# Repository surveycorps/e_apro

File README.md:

e_apro
======

The electrical subsytems schematics, BOM, board files
- usb_hub is a 7 port usb hub based off of TI's TUSB2077A
- audio is a usb audio codec based off the PCM2912A
- gps is a usb powered gps module based off the Jupiter SE880
- screen is a hdmi to tft screen converter using TFP401A
- motor is a motor driver with F2V converters
- powers provides power regulator based off LM3478
- apro_lib contains all the custom symbols and footprints used
- eagle contains the files for connecting the various breakoutboards

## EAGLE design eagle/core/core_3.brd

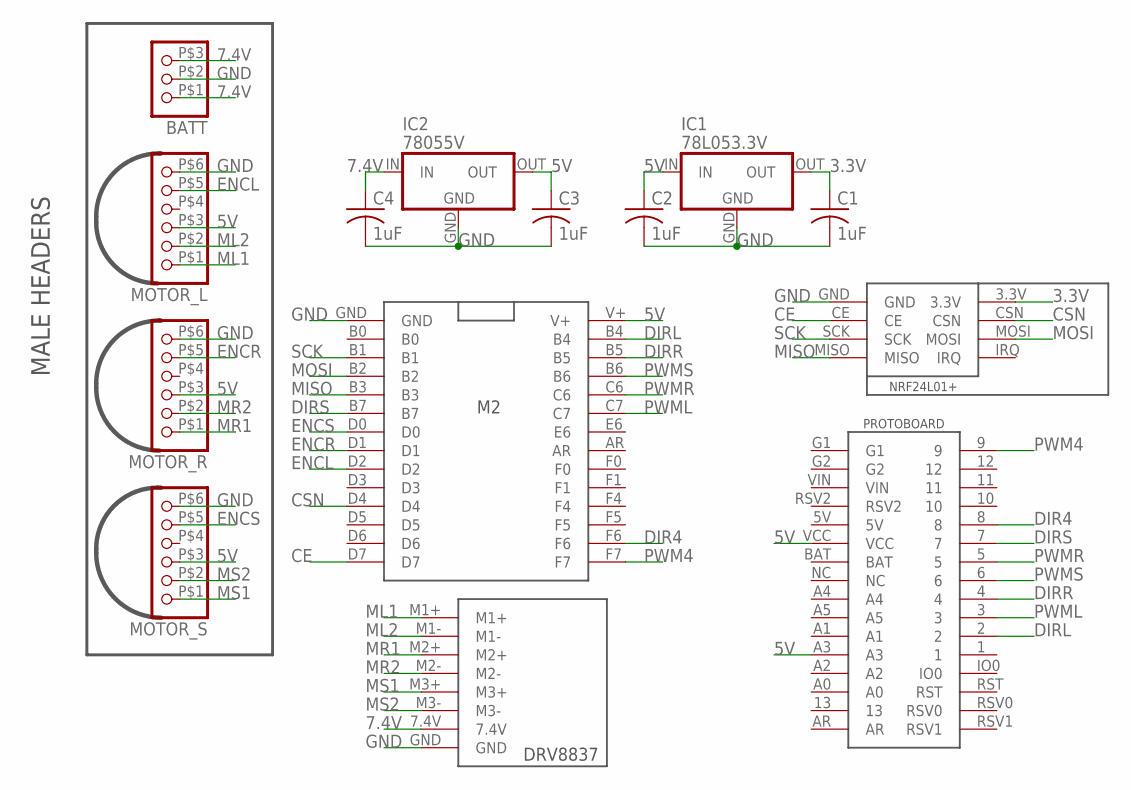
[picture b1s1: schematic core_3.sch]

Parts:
BATT: PINHD-1X3SMD; 1X3/90SMD
C1, C2, C3, C4: 1uF; C025-030X050
IC1: 78L053.3V; TO92
IC2: 78055V; TO220H
MOTOR_L: PINHD-1X6SMD; 1X6/90SMD
MOTOR_R: PINHD-1X6SMD; 1X6/90SMD
MOTOR_S: PINHD-1X6SMD; 1X6/90SMD
U$1: NRF24L01
U$2: M2
U$3: PROTOBOARDSMD; PROTOSMD
U$4: DRV8837

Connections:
3.3V: C1.1, IC1.OUT, U$1.3.3V
5V: C2.1, C3.1, IC1.IN, IC2.OUT, MOTOR_L.P$3 (3), MOTOR_R.P$3 (3), MOTOR_S.P$3 (3), U$2.V+, U$3.A3, U$3.VCC
7.4V: BATT.P$1 (1), BATT.P$3 (3), C4.1, IC2.IN, U$4.7.4V
CE: U$1.CE, U$2.D7
CSN: U$1.CSN, U$2.D4
DIR4: U$2.F6, U$3.8
DIRL: U$2.B4, U$3.2
DIRR: U$2.B5, U$3.4
DIRS: U$2.B7, U$3.7
ENCL: MOTOR_L.P$5 (5), U$2.D2
ENCR: MOTOR_R.P$5 (5), U$2.D1
ENCS: MOTOR_S.P$5 (5), U$2.D0
GND: BATT.P$2 (2), C1.2, C2.2, C3.2, C4.2, IC1.GND, IC2.GND, MOTOR_L.P$6 (6), MOTOR_R.P$6 (6), MOTOR_S.P$6 (6), U$1.GND, U$2.GND, U$4.GND
MISO: U$1.MISO, U$2.B3
ML1: MOTOR_L.P$1 (1), U$4.M1+
ML2: MOTOR_L.P$2 (2), U$4.M1-
MOSI: U$1.MOSI, U$2.B2
MR1: MOTOR_R.P$1 (1), U$4.M2+
MR2: MOTOR_R.P$2 (2), U$4.M2-
MS1: MOTOR_S.P$1 (1), U$4.M3+
MS2: MOTOR_S.P$2 (2), U$4.M3-
PWM4: U$2.F7, U$3.9
PWML: U$2.C7, U$3.3
PWMR: U$2.C6, U$3.5
PWMS: U$2.B6, U$3.6
SCK: U$1.SCK, U$2.B1

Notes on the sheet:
MALE HEADERS

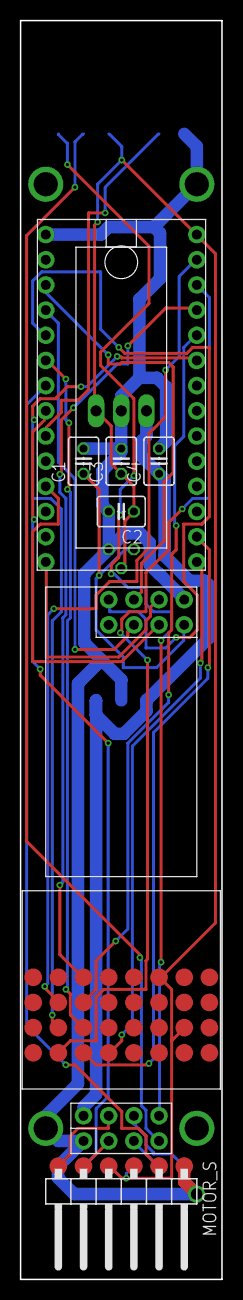
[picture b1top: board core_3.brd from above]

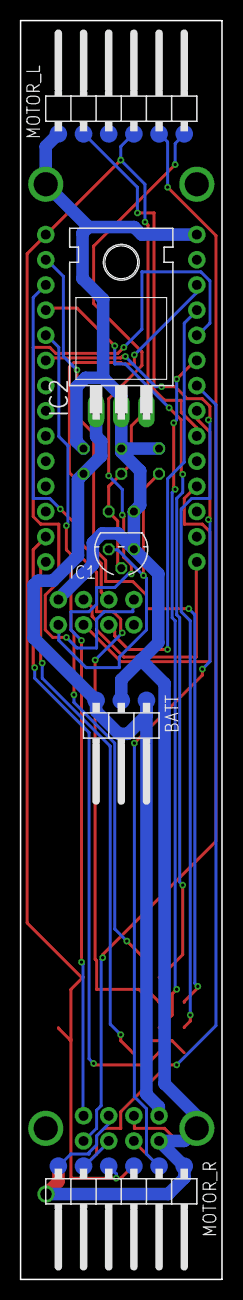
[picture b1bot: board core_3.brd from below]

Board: 2 copper layers, 20.3 x 127.0 mm, 14 parts (5 on the bottom side), 26 nets.

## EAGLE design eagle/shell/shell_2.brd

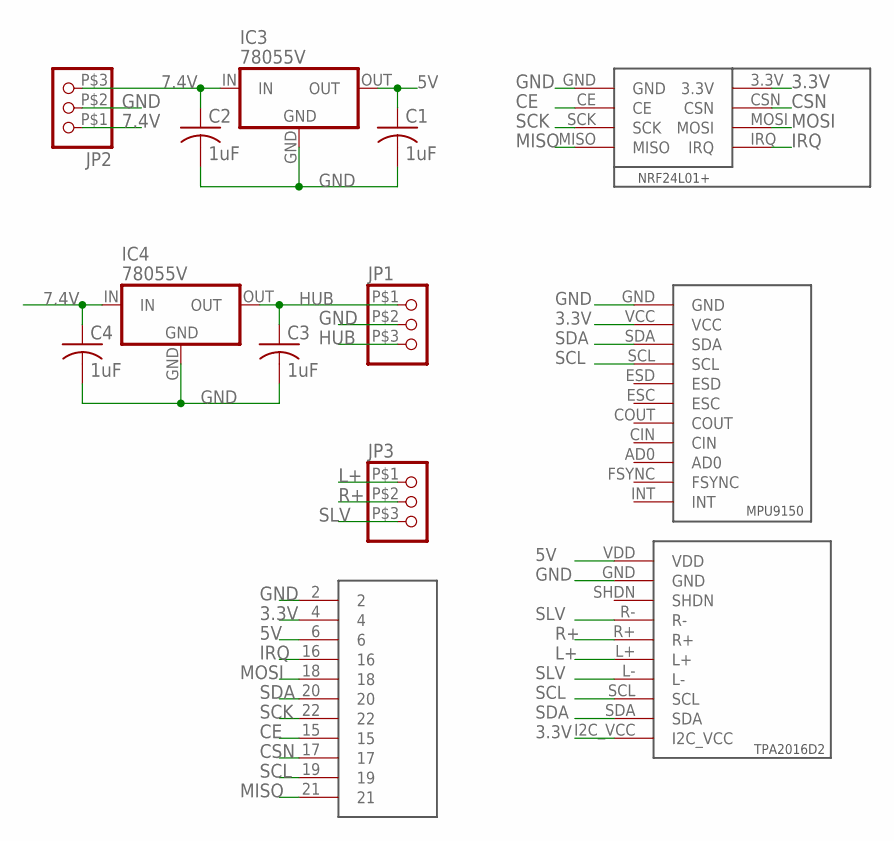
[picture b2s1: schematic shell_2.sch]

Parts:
C1, C2, C3, C4: 1uF; C050-024X044
IC3, IC4: 78055V; TO220H
JP1, JP2, JP3: PINHD-1X3SMD; 1X3/90SMD
JP4: PINHD-1X11SMD; 1X11/90_2
U$1: MPU9150
U$2: NRF24L01
U$3: TPA2016D2

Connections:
3.3V: JP4.4, U$1.VCC, U$2.3.3V, U$3.I2C_VCC
5V: C1.1, IC3.OUT, JP4.6, U$3.VDD
7.4V: C2.1, C4.1, IC3.IN, IC4.IN, JP2.P$1 (1), JP2.P$3 (3)
CE: JP4.15, U$2.CE
CSN: JP4.17, U$2.CSN
GND: C1.2, C2.2, C3.2, C4.2, IC3.GND, IC4.GND, JP1.P$2 (2), JP2.P$2 (2), JP4.2, U$1.GND, U$2.GND, U$3.GND
HUB: C3.1, IC4.OUT, JP1.P$1 (1), JP1.P$3 (3)
IRQ: JP4.16, U$2.IRQ
L+: JP3.P$1 (1), U$3.L+
MISO: JP4.21, U$2.MISO
MOSI: JP4.18, U$2.MOSI
R+: JP3.P$2 (2), U$3.R+
SCK: JP4.22, U$2.SCK
SCL: JP4.19, U$1.SCL, U$3.SCL
SDA: JP4.20, U$1.SDA, U$3.SDA
SLV: JP3.P$3 (3), U$3.L-, U$3.R-

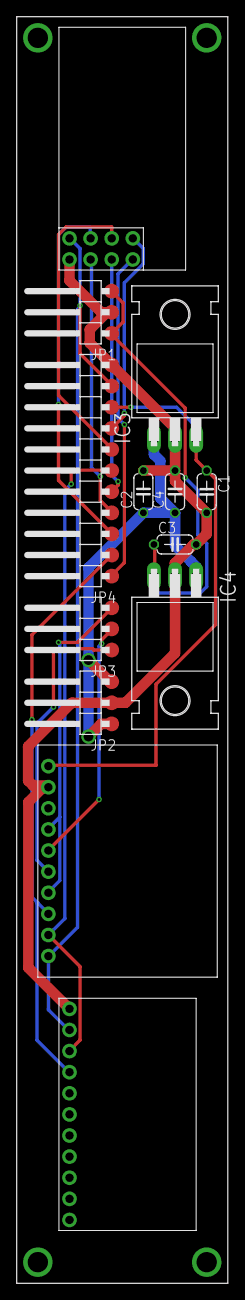
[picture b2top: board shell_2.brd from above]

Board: 2 copper layers, 25.4 x 152.4 mm, 13 parts (0 on the bottom side), 16 nets.

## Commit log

2014-09-16 added pdf of schematic
2014-09-20 crystal and ferrite bead
2014-09-20 crystals and ferrite beads for real this time
2014-09-21 started external mic board and audio pcb
2014-09-21 started pcb design for usb hub
2014-09-22 need to not waste as much space on board
2014-09-22 audio pcb updates
2014-09-23 made thinner approx 1x4
2014-09-23 finishing audio pcb layout
2014-09-23 updating readme file
2014-09-24 added logo mod, updated audio pcb, and finished micboard
2014-09-24 finished the usb_hub
2014-09-25 intial commit for gps module
2014-09-26 updating audio board to change vias
2014-09-26 correcting audio board vias
2014-09-27 added the TFP401A symbol
2014-09-27 now using the SE880 GPS
2014-09-28 finished gps schematic. need to create footprints
2014-09-28 added logo image
2014-09-29 made most of the gps footprints
2014-09-30 usb_hub ready for manufacturing
2014-09-30 finalizing audio board
2014-09-30 usb_hub final. fixed annular ring clearance
2014-09-30 moved the trace away from the edge
2014-10-01 finished the gps schematic. need to finish BOM. Preliminary work on board
2014-10-01 changed mic. board done...i hope
2014-10-01 board is ready
2014-10-04 added jumpers to switch communication method
2014-10-06 initial commit of screen schematic
2014-10-07 fixed pin 47 to gnd. need to clip and solder to adjacent pin
2014-10-07 need to place all components on bottom and create analog ground plane for antenna
2014-10-07 fixed the bom so it shows up nicely
2014-10-07 finishing up schematic and starting board footprints and design
2014-10-08 modeled the 50ohm trace as grounded coplanar. need to move things around better so it can solve
2014-10-08 finished component modules and started screen board design
2014-10-09 moving around some stuff for routing
2014-10-11 fixed audio bom
2014-10-11 added usb_hub bom
2014-10-16 finished routing. need to add stitching vias
2014-10-17 screen board is complete
2014-10-17 added bom
2014-10-19 Finished the GPS module
2014-10-19 Finished usb_hub revision B. Less complex, less that can go wrong
2014-10-19 started motor driver schematic
2014-10-19 removing extra readme
2014-10-28 finalizing components for 5v5a
2014-10-28 motor schematic almost finished
2014-11-03 started design for pick and place
2014-11-04 Moving all the symbols and footprints in a common library. Changed a few components so we have less reels to buy for pick and place. Changing amplifier to a more supported one from TI.
2014-11-06 finished routing. need to check bom and trace widths and pos file
2014-11-10 usb_hub ready for review. Audio schematic in the works
2014-11-10 need to add required fields for assembly
2014-11-11 sent usb_hub for review. Finished gps schematic/bom.
2014-11-12 adding fields to audio schematic
2014-11-13 finished schematic. need to route board and send BOM
2014-11-14 finished board layout. Ready for review
2014-11-14 placed all components on one side to make assembly easier. Ready for review
2014-11-14 Need to route the 50ohm trace
2014-11-15 cleaned up the usb hub project. waiting quote on elecrow
2015-03-20 added eagle files that are used to connect the various store bought breakout boards so that we can finish the project on time
